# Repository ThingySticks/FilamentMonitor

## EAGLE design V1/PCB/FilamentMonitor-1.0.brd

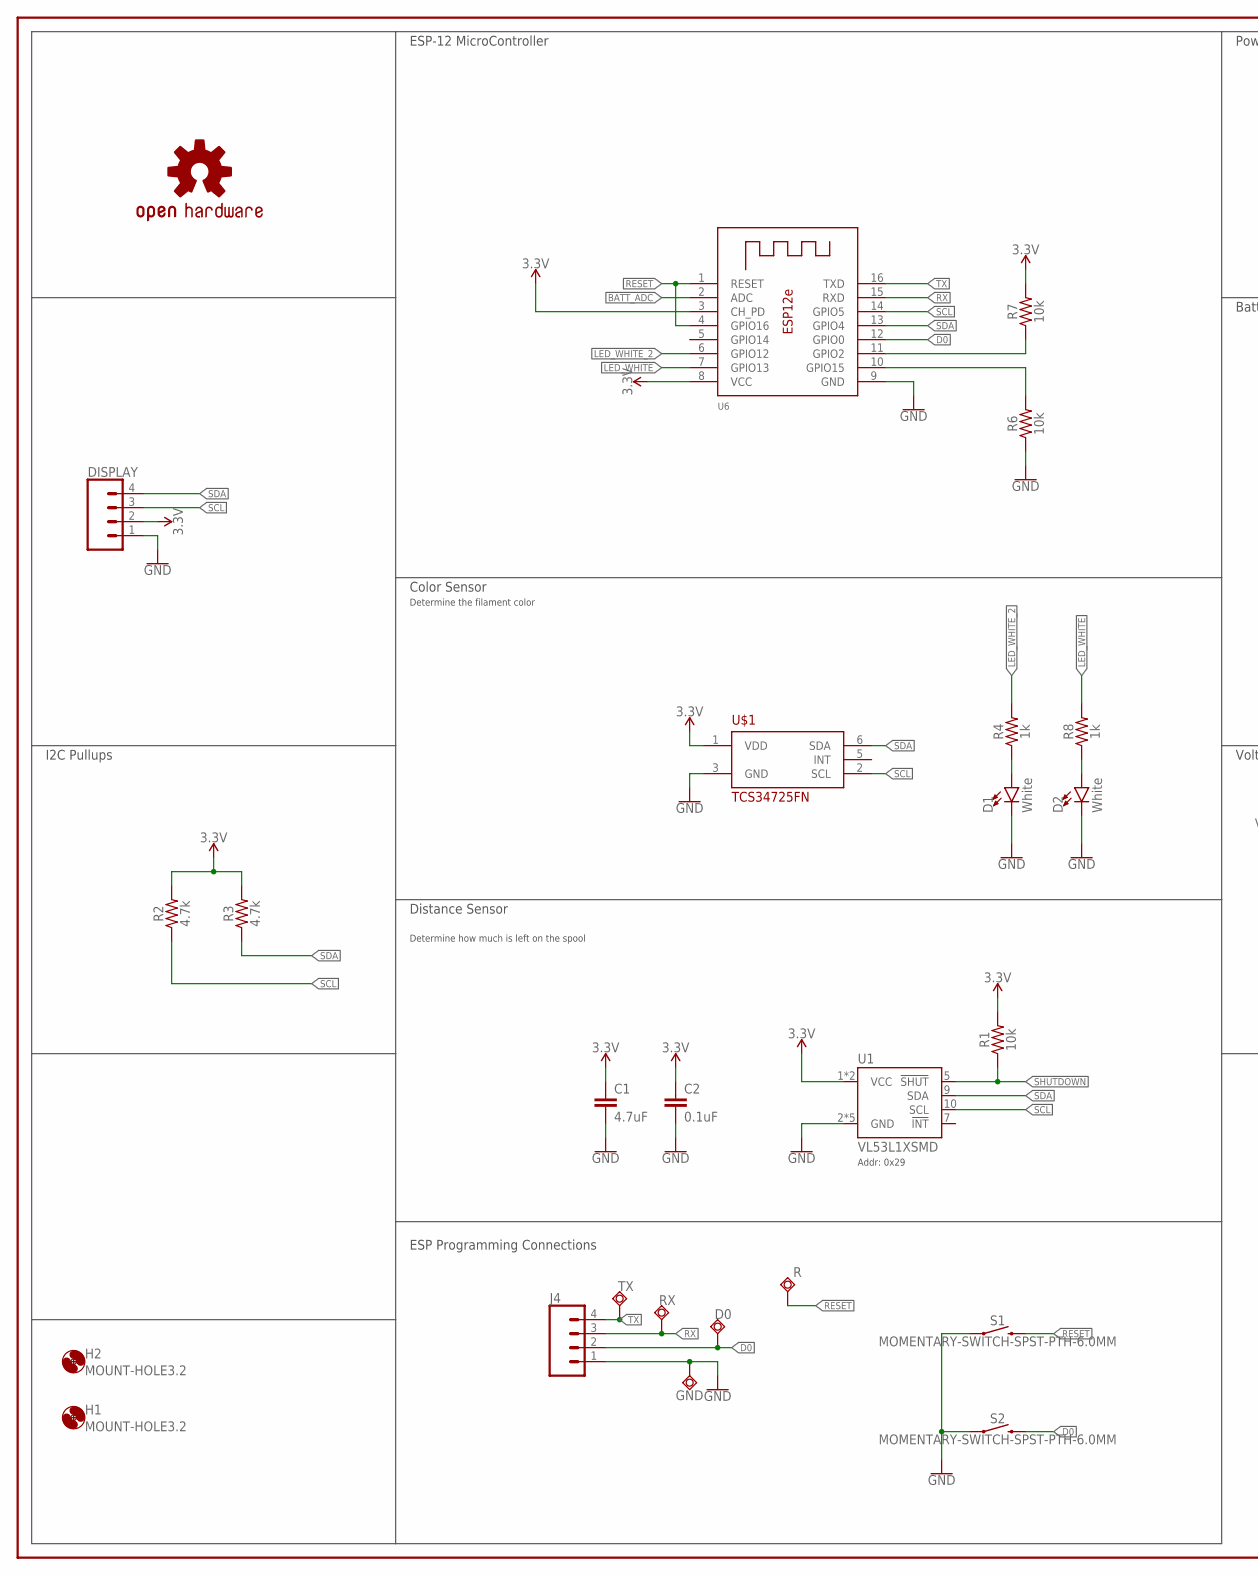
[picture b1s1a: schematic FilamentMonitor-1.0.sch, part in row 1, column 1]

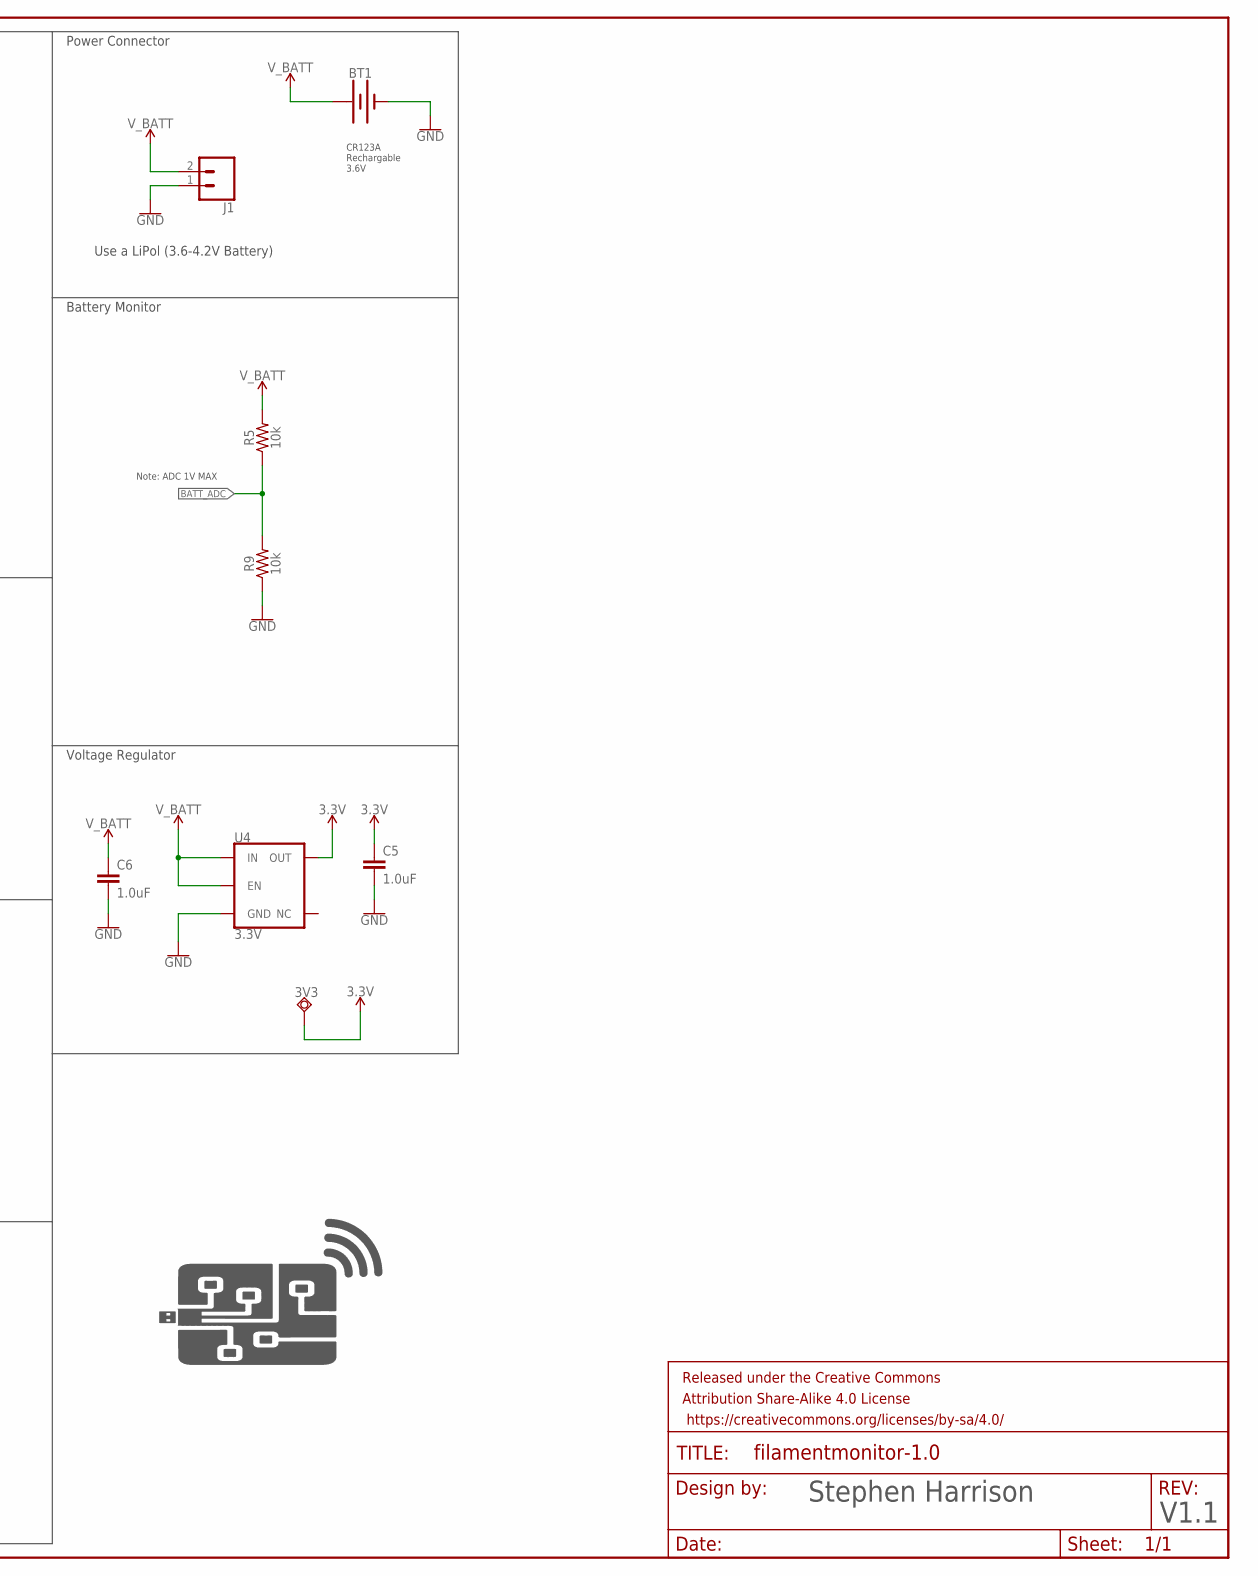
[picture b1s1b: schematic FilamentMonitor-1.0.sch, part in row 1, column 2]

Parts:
3V3: TPSQTP10SQ; TP10SQ
BT1: BATTERY-16340; BATTERY_16340-HOLDER
C1: 4.7uF; 0603
C2: 0.1uF; 0603
C5, C6: 1.0uF; 0603
D0: TPSQTP10SQ; TP10SQ
D1, D2: White; LED-1206
DISPLAY: CONN_04; 1X04
FRAME1: FRAME-LEDGER; CREATIVE_COMMONS
GND: TPSQTP10SQ; TP10SQ
H1, H2: MOUNT-HOLE3.2; 3,2
J1: CONN_02-JST-2MM-SMT; JST-2-SMD
J4: CONN_04; 1X04
LOGO1: OSHW-LOGOL; OSHW-LOGO-L
R: TPSQTP10SQ; TP10SQ
R1, R5, R6, R7, R9: 10k; 0603
R2, R3: 4.7k; 0603
R4, R8: 1k; 0805
RX: TPSQTP10SQ; TP10SQ
S1, S2: MOMENTARY-SWITCH-SPST-PTH-6.0MM; TACTILE_SWITCH_PTH_6.0MM
TX: TPSQTP10SQ; TP10SQ
U1: VL53L1XSMD; VL53L1X
U4: 3.3V; SOT23-5
U6: ESP-12E
U$1: TCS34725FN; FN-6
U$2: THINGYSTICKS_LOGO

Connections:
3.3V: 3V3.TP, C1.1, C2.1, C5.1, DISPLAY.2, R1.2, R2.2, R3.2, R7.2, U1.1 (VCC), U1.11 (VCC), U4.5 (OUT), U6.3 (CH_PD), U6.8 (VCC), U$1.1 (VDD)
ACCEL_INT_2: R7.1, U6.11 (GPIO2)
BATT_ADC: R5.1, R9.2, U6.2 (ADC)
D0: D0.TP, J4.2, S2.3 (2), U6.12 (GPIO0)
GND: BT1.P$2 (-), C1.2, C2.2, C5.2, C6.2, D1.C, D2.C, DISPLAY.1, GND.TP, J1.1 (2), J4.1, R6.1, R9.1, S1.1, S2.1, U1.2 (GND), U1.3 (GND), U1.4 (GND), U1.6 (GND), U1.12 (GND), U4.2 (GND), U6.9 (GND), U$1.3 (GND)
GPIO15: R6.2, U6.10 (GPIO15)
LED_WHITE: R8.2, U6.7 (GPIO13)
LED_WHITE_2: R4.2, U6.6 (GPIO12)
unnamed: D2.A, R8.1
unnamed: D1.A, R4.1
RESET: R.TP, S1.3 (2), U6.1 (RESET), U6.4 (GPIO16)
RX: J4.3, RX.TP, U6.15 (RXD)
SCL: DISPLAY.3, R2.1, U1.10 (SCL), U6.14 (GPIO5), U$1.2 (SCL)
SDA: DISPLAY.4, R3.1, U1.9 (SDA), U6.13 (GPIO4), U$1.6 (SDA)
SHUTDOWN: R1.1, U1.5 (!SHUT)
TX: J4.4, TX.TP, U6.16 (TXD)
V_BATT: BT1.P$1 (+), C6.1, J1.2 (1), R5.2, U4.1 (IN), U4.3 (EN)

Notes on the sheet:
Addr: 0x29
ESP Programming Connections
I2C Pullups
Power Connector
Use a LiPol (3.6-4.2V Battery)
ESP-12 MicroController
Color Sensor
Distance Sensor
Voltage Regulator
Battery Monitor
Stephen Harrison
V1.1
Determine how much is left on the spool
Determine the filament color
Note: ADC 1V MAX
CR123A Rechargable 3.6V

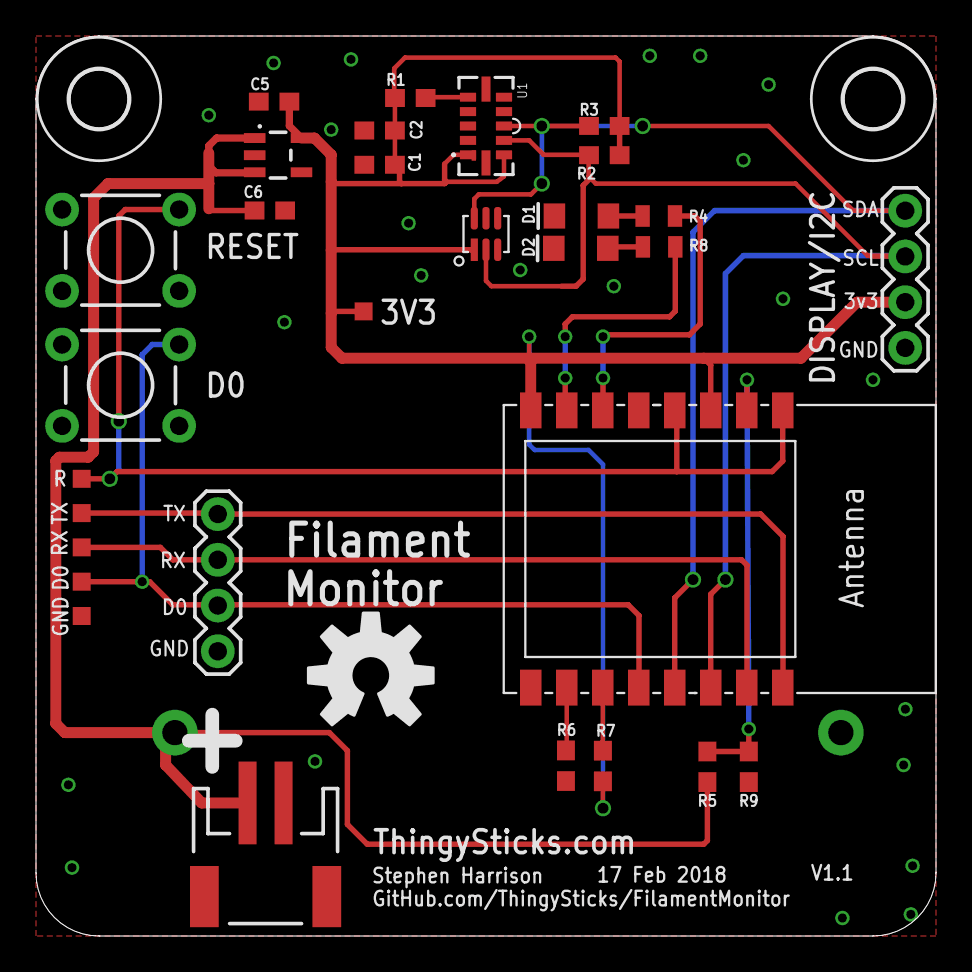
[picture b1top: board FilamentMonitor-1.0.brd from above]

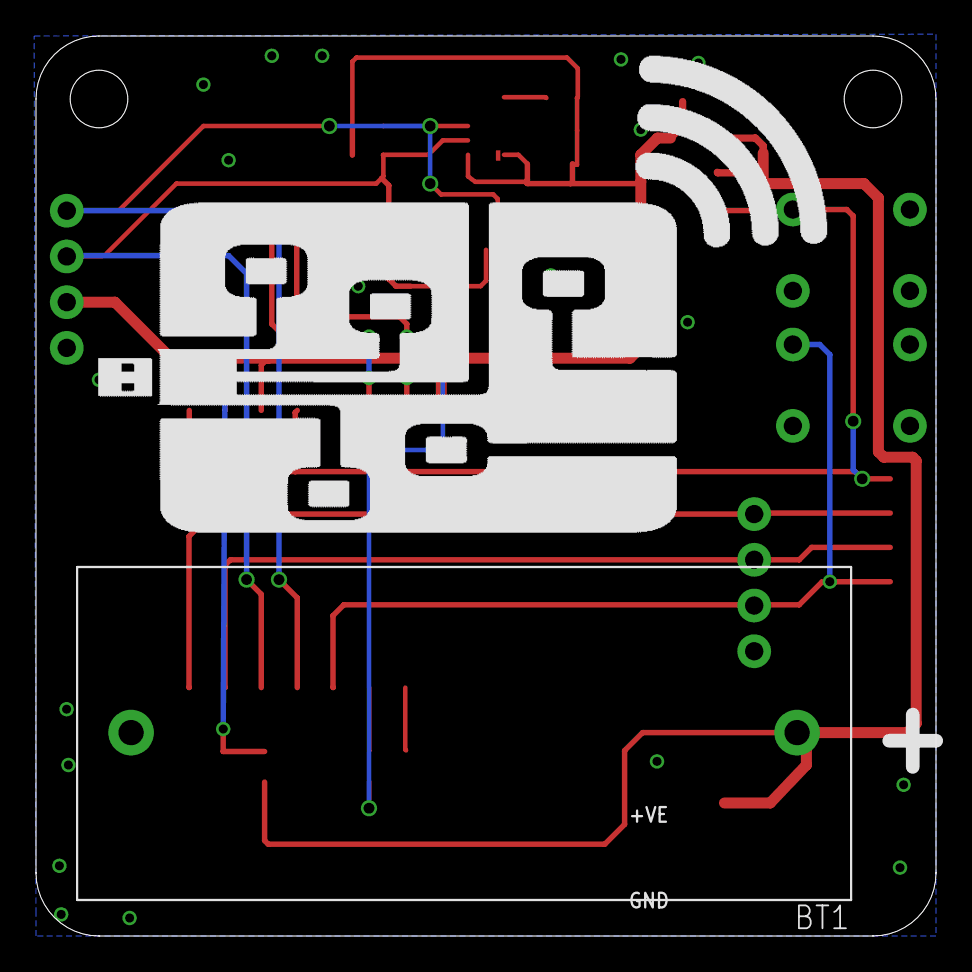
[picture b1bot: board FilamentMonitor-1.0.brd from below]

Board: 2 copper layers, 50.0 x 50.0 mm, 36 parts (2 on the bottom side), 17 nets.

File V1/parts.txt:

Partlist

Exported from FilamentMonitor-1.0.brd at 17/02/2019 15:57

EAGLE Version 7.4.0 Copyright (c) 1988-2015 CadSoft

Assembly variant: 

Part     Value                           Package                  Library             Position (mm)         Orientation

3V3      TPSQTP10SQ                      TP10SQ                   testpad             (18.2 34.7)           R0
BT1                                      BATTERY_16340-HOLDER     ThingySticks        (4.7175 20.5)         MR180
C1       4.7uF                           0603                     SparkFun-Capacitors (19.09 42.845)        R180
C2       0.1uF                           0603                     SparkFun-Capacitors (19.09 44.75)         R180
C5       1.0uF                           0603                     SparkFun-Capacitors (13.225 46.355)       R180
C6       1.0uF                           0603                     SparkFun-Capacitors (12.99 40.305)        R0
D0       TPSQTP10SQ                      TP10SQ                   testpad             (2.54 19.685)         R0
D1       White                           LED-1206                 SparkFun-LED        (30.3 40)             R180
D2       White                           LED-1206                 SparkFun-LED        (30.265 38.205)       R180
DISPLAY                                  1X04                     ThingySticks        (48.29 32.6725)       R90
GND      TPSQTP10SQ                      TP10SQ                   testpad             (2.54 17.78)          R180
J1                                       JST-2-SMD                SparkFun-Connectors (12.755 3.69)         R180
J4                                       1X04                     ThingySticks        (10.1 15.82)          R90
R        TPSQTP10SQ                      TP10SQ                   testpad             (2.54 25.4)           R180
R1       10k                             0603                     SparkFun-Resistors  (20.795 46.555)       R180
R2       4.7k                            0603                     SparkFun-Resistors  (31.5725 43.38)       R0
R3       4.7k                            0603                     SparkFun-Resistors  (31.5725 45.0025)     R0
R4       1k                              0805                     SparkFun-Resistors  (34.6 40)             R0
R5       10k                             0603                     SparkFun-Resistors  (37.3 9.4)            R270
R6       10k                             0603                     SparkFun-Resistors  (29.44 9.46)          R90
R7       10k                             0603                     SparkFun-Resistors  (31.495 9.445)        R270
R8       1k                              0805                     SparkFun-Resistors  (34.6175 38.285)      R0
R9       10k                             0603                     SparkFun-Resistors  (39.6 9.4)            R90
RX       TPSQTP10SQ                      TP10SQ                   testpad             (2.54 21.59)          R0
S1       MOMENTARY-SWITCH-SPST-PTH-6.0MM TACTILE_SWITCH_PTH_6.0MM SparkFun-Switches   (4.7 38.1)            R180
S2       MOMENTARY-SWITCH-SPST-PTH-6.0MM TACTILE_SWITCH_PTH_6.0MM SparkFun-Switches   (4.7 30.6)            R180
TX       TPSQTP10SQ                      TP10SQ                   testpad             (2.54 23.495)         R0
U$1      TCS34725FN                      FN-6                     ThingySticks        (25 39)               R90
U1       VL53L1XSMD                      VL53L1X                  SparkFun-Sensors    (25 45)               R270
U4       3.3V                            SOT23-5                  SparkFun-IC-Power   (13.45 43.38)         R270
U6                                       ESP-12E                  kanflo              (36.985 21.5)         R270

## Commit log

2019-02-17 First version...

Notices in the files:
parts and their libraries:
SparkFun-Sensors: Licensing: Creative Commons ShareAlike 4.0 International - https://creativecommons.org/licenses/by-sa/4.0
SparkFun-Aesthetics: Released under the Creative Commons Attribution Share-Alike 4.0 License
SparkFun-Aesthetics: https://creativecommons.org/licenses/by-sa/4.0
